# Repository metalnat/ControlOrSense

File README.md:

# ControlOrSense
The project files for my Control Or Sense experiment

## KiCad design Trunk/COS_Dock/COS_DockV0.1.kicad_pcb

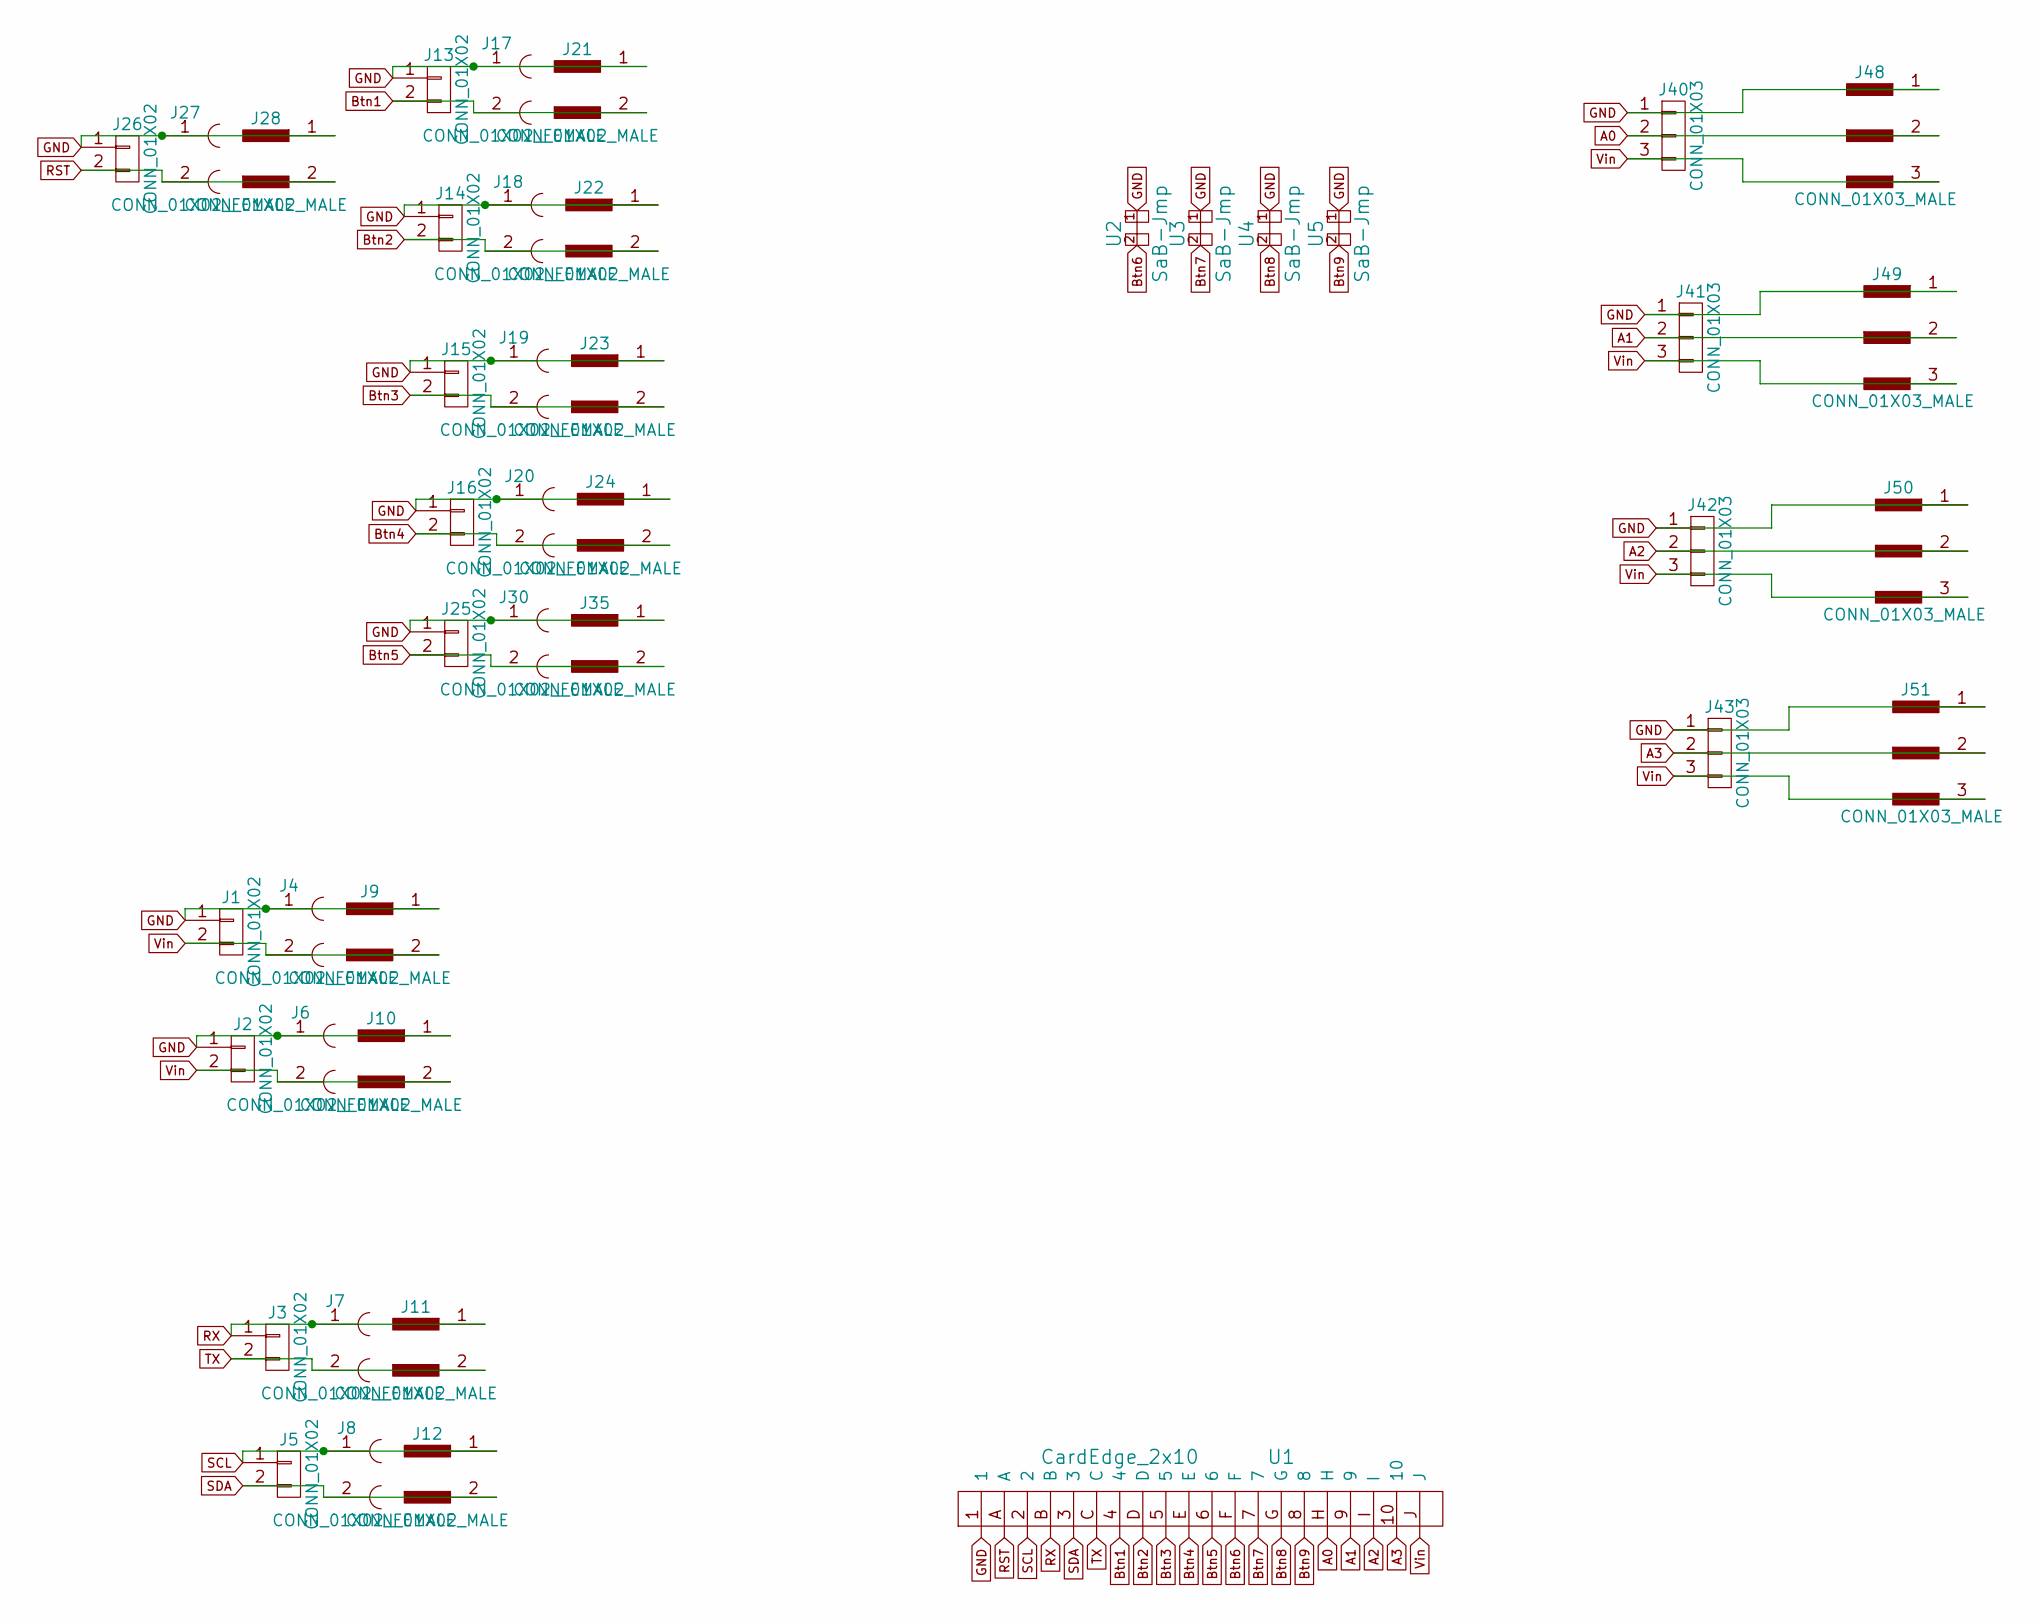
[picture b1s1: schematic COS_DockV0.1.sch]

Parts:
J1, J2, J3, J5, J13, J14, J15, J16, J25, J26: CONN_01X02; Pin_Header_Straight_1x02_Pitch2.54mm
J4, J6, J7, J8, J17, J18, J19, J20, J27, J30: CONN_01X02_FEMALE; SMD-2512_Pol
J9, J10, J11, J12, J21, J22, J23, J24, J28, J35: CONN_01X02_MALE; JST_ZE_BM02B-ZESS-TBT_02x1.5mm_Straight
J40, J41, J42, J43: CONN_01X03; Pin_Header_Straight_1x03_Pitch2.54mm
J48, J49, J50, J51: CONN_01X03_MALE; JST_ZE_BM03B-ZESS-TBT_03x1.5mm_Straight
U1: CardEdge_2x10; CardEdge_10x2_DOCK
U2, U3, U4, U5: SaB-Jmp; GS2

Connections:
A0: J40.2, J48.2, U1.H
A1: J41.2, J49.2, U1.9
A2: J42.2, J50.2, U1.I
A3: J43.2, J51.2, U1.10
Btn1: J13.2, J17.2, J21.2, U1.4
Btn2: J14.2, J18.2, J22.2, U1.D
Btn3: J15.2, J19.2, J23.2, U1.5
Btn4: J16.2, J20.2, J24.2, U1.E
Btn5: J25.2, J30.2, J35.2, U1.6
Btn6: U1.F, U2.2
Btn7: U1.7, U3.2
Btn8: U1.G, U4.2
Btn9: U1.8, U5.2
GND: J1.1, J2.1, J4.1, J6.1, J9.1, J10.1, J13.1, J14.1, J15.1, J16.1, J17.1, J18.1, J19.1, J20.1, J21.1, J22.1, J23.1, J24.1, J25.1, J26.1, J27.1, J28.1, J30.1, J35.1, J40.1, J41.1, J42.1, J43.1, J48.1, J49.1, J50.1, J51.1, U1.1, U2.1, U3.1, U4.1, U5.1
RST: J26.2, J27.2, J28.2, U1.A
RX: J3.1, J7.1, J11.1, U1.B
SCL: J5.1, J8.1, J12.1, U1.2
SDA: J5.2, J8.2, J12.2, U1.3
TX: J3.2, J7.2, J11.2, U1.C
Vin: J1.2, J2.2, J4.2, J6.2, J9.2, J10.2, J40.3, J41.3, J42.3, J43.3, J48.3, J49.3, J50.3, J51.3, U1.J

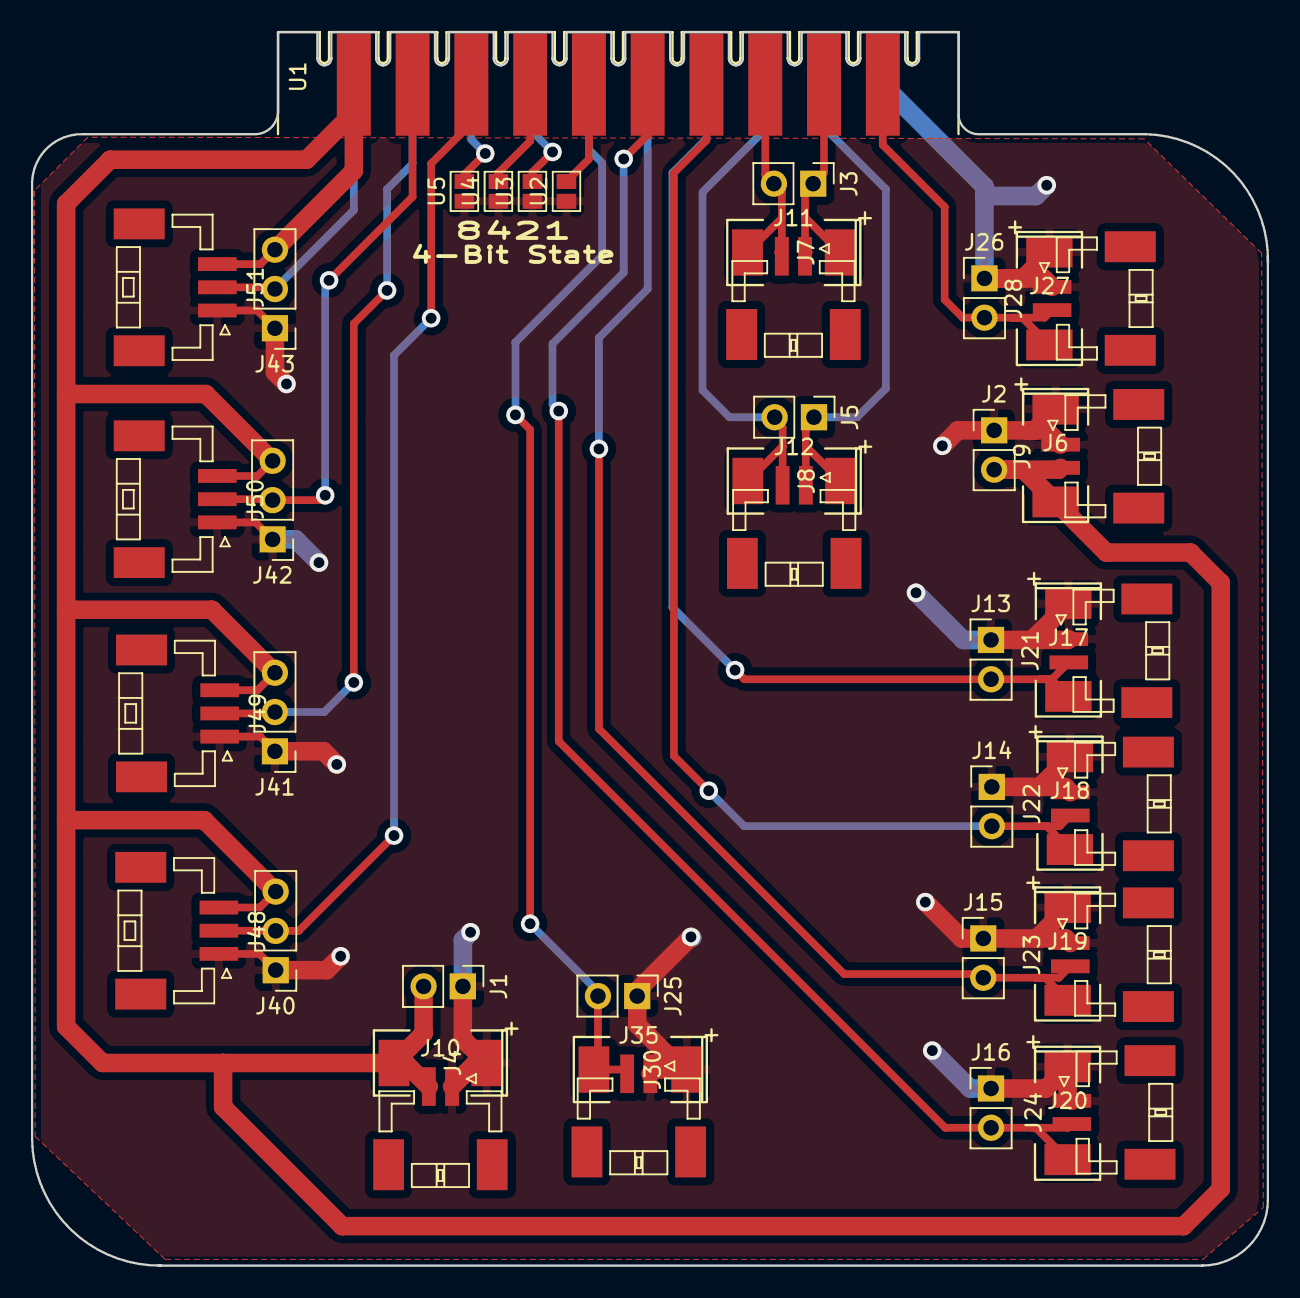
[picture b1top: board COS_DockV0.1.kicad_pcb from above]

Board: 2 copper layers, 79.9 x 79.8 mm, 43 parts (0 on the bottom side), 20 nets.

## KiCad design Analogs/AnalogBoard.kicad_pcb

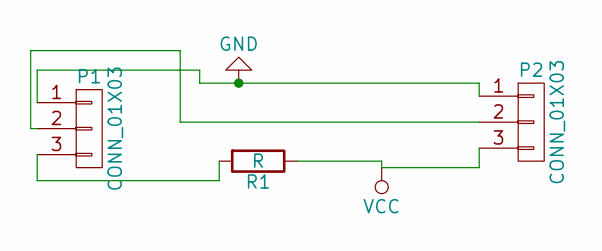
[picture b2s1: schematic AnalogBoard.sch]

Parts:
P1, P2: CONN_01X03; Molex_KK-6410-03_03x2.54mm_Straight
R1: R; R_Axial_DIN0204_L3.6mm_D1.6mm_P7.62mm_Horizontal

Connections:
GND: P1.1, P2.1
unnamed: P1.2, P2.2
unnamed: P1.3, R1.2
VCC: P2.3, R1.1

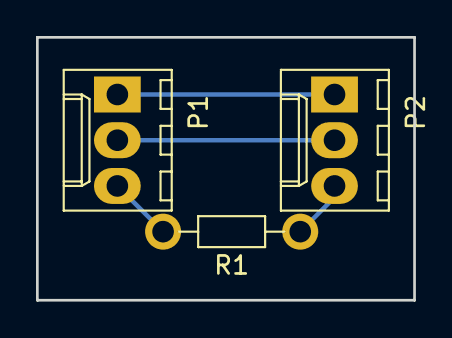
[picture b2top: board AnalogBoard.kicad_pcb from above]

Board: 2 copper layers, 21.0 x 14.6 mm, 3 parts (0 on the bottom side), 4 nets.

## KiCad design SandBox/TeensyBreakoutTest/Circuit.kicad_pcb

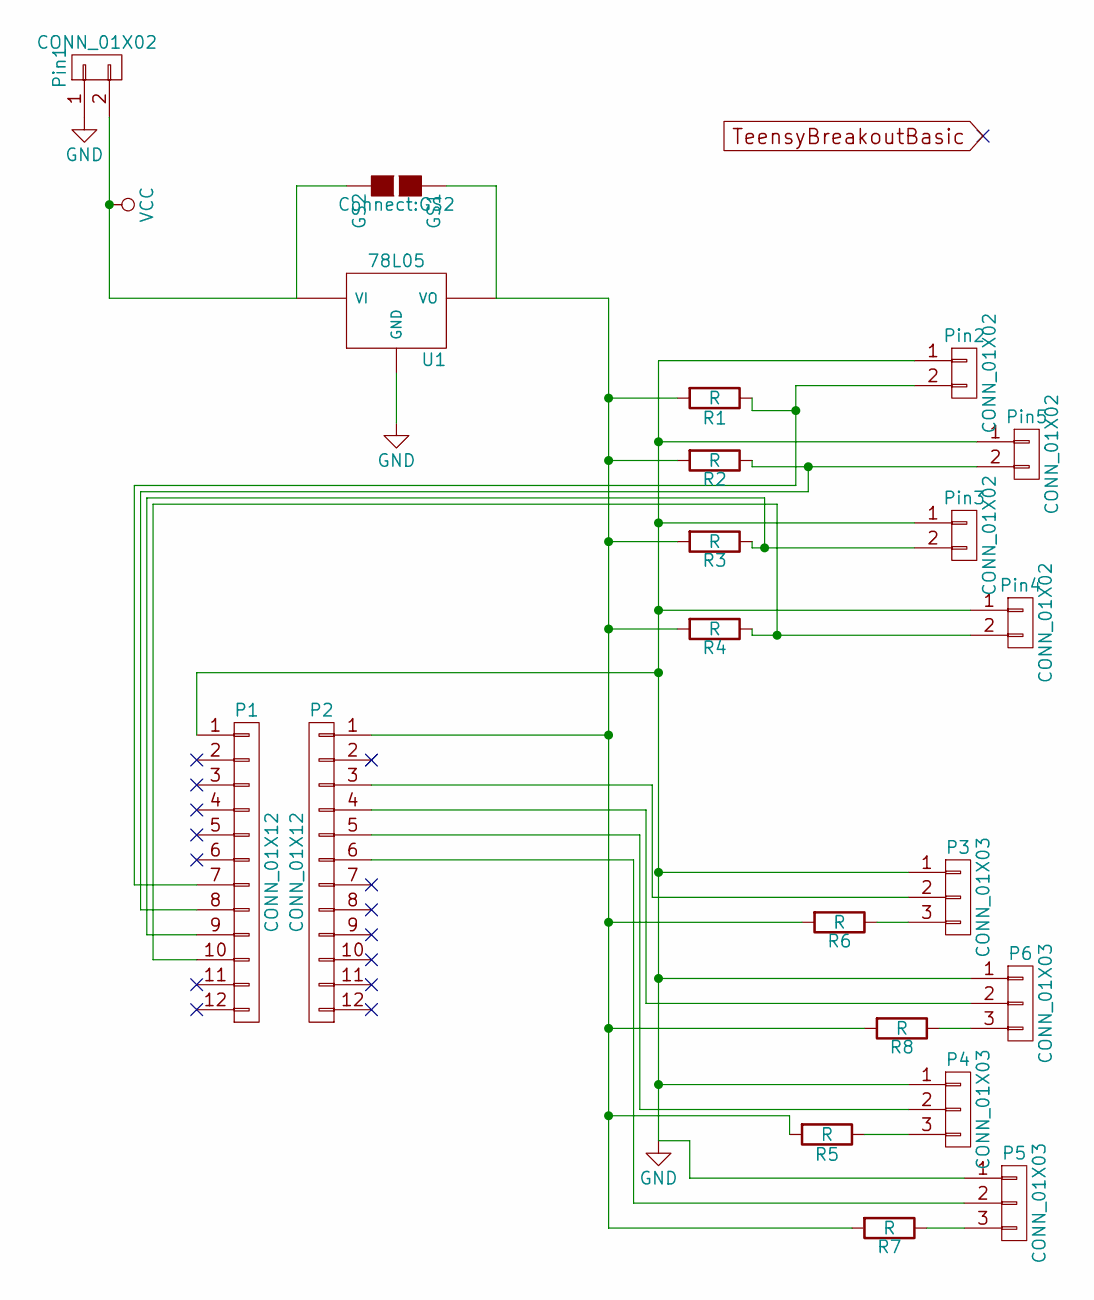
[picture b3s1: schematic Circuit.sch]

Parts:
GS1: GS2
P1, P2: CONN_01X12; Pin_Header_Straight_1x12_Pitch1.27mm
P3, P4, P5, P6: CONN_01X03; Molex_KK-6410-03_03x2.54mm_Straight
Pin1, Pin2, Pin3, Pin4, Pin5: CONN_01X02; Molex_KK-6410-02_02x2.54mm_Straight
R1, R2, R3, R4, R5, R6, R7, R8: R; R_0805_HandSoldering
U1: 78L05; Socket_MOLEX-KK-RM3-96mm_Lock_3pin_straight

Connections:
GND: P1.1, P3.1, P4.1, P5.1, P6.1, Pin1.1, Pin2.1, Pin3.1, Pin4.1, Pin5.1, U1.GND
unnamed: GS1.1 (G1), P2.1, R1.2, R2.2, R3.2, R4.2, R5.2, R6.2, R7.2, R8.2, U1.VO
unnamed: P1.7, Pin2.2, R1.1
unnamed: P1.8, Pin5.2, R2.1
unnamed: P1.9, Pin3.2, R3.1
unnamed: P1.10, Pin4.2, R4.1
unnamed: P2.3, P3.2
unnamed: P2.4, P6.2
unnamed: P2.5, P4.2
unnamed: P2.6, P5.2
unnamed: P3.3, R6.1
unnamed: P4.3, R5.1
unnamed: P5.3, R7.1
unnamed: P6.3, R8.1
VCC: GS1.2 (G2), Pin1.2, U1.VI

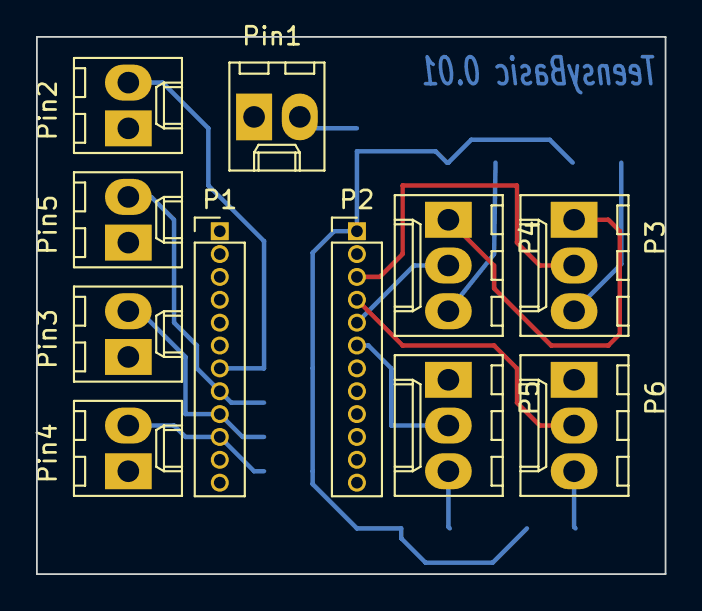
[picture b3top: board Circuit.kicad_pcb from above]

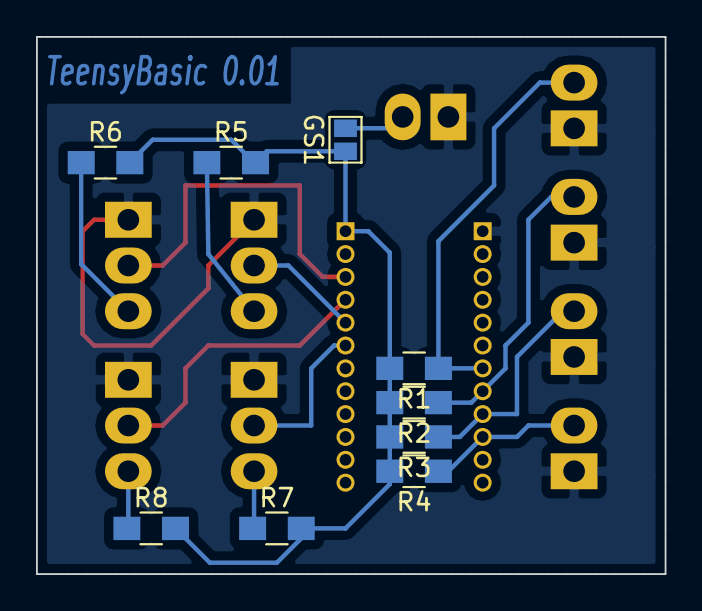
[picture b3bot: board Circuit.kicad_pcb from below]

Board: 2 copper layers, 34.9 x 29.8 mm, 20 parts (9 on the bottom side), 15 nets.

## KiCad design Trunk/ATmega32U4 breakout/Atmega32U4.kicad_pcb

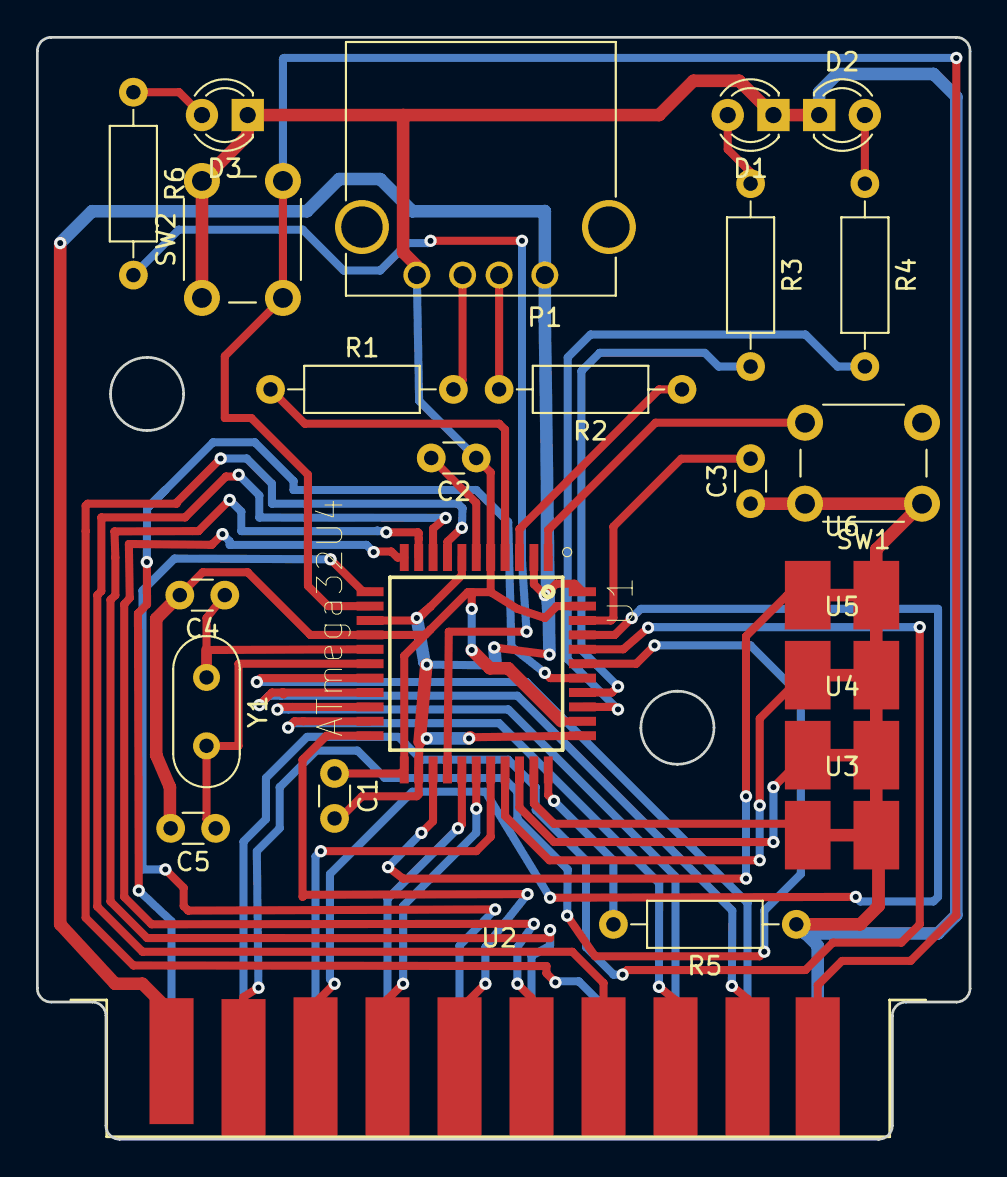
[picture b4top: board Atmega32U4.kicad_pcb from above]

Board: 2 copper layers, 51.8 x 61.2 mm, 24 parts (0 on the bottom side), 36 nets.

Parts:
C1, C2: 1uf; C_Disc_D3.0mm_W1.6mm_P2.50mm
C3: .1uf; C_Disc_D3.0mm_W1.6mm_P2.50mm
C4, C5: 10pf; C_Disc_D3.0mm_W1.6mm_P2.50mm
D1: LedIndicator01; LED_D3.0mm
D2: LedIndicator02; LED_D3.0mm
D3: Led_Small; LED_D3.0mm
P1: USB; USB_A
R1, R2: 22R; R_Axial_DIN0207_L6.3mm_D2.5mm_P10.16mm_Horizontal
R3, R4: 220; R_Axial_DIN0207_L6.3mm_D2.5mm_P10.16mm_Horizontal
R5, R6: 1K; R_Axial_DIN0207_L6.3mm_D2.5mm_P10.16mm_Horizontal
SW1: BtnLocal; SW_PUSH_6mm
SW2: Reset Btn; SW_PUSH_6mm
U1: ATmega32U4; QFP80P1200X1200X120-44N
U2: CardEdge_2x10; CardEdge_10x2
U3, U4, U5, U6: SlashAndBurn-Jumper
Y1: 16MHz; Crystal_HC52-6mm_Vertical

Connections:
+3V3: C2.2, U1.6
+5V: C1.2, P1.1, U1.2, U1.7, U1.14, U1.24, U1.34, U1.44, U2.J
A0: U1.41, U2.H
A1: U1.40, U2.9
A2: U1.39, U2.I
A3: U1.38, U2.10
Btn1: U1.8, U2.4
Btn2: U1.9, U2.D
Btn3: U1.10, U2.5
Btn4: U1.11, U2.E
Btn5: U1.12, U2.6
Btn6: U1.22, U2.F
Btn7: U1.27, U2.7
Btn8: U1.28, U2.G
Btn9: U1.29, U2.8
GND: C1.1, C2.1, C3.1, C4.2, C5.2, D1.1, D2.1, D3.1, P1.4, R5.1, SW1.1, SW2.1, U1.5, U1.15, U1.23, U1.25, U1.30, U1.31, U1.32, U1.35, U1.43, U2.1, U3.1, U3.2, U4.1, U4.2, U5.1, U5.2, U6.1, U6.2
unnamed: C3.2, U1.42
unnamed: C4.1, U1.16, Y1.1
unnamed: C5.1, U1.17, Y1.2
unnamed: D1.2, R3.1
unnamed: D2.2, R4.1
unnamed: D3.2, R6.1
unnamed: P1.2, R2.2
unnamed: P1.3, R1.2
unnamed: R1.1, U1.4
unnamed: R2.1, U1.3
unnamed: R3.2, U1.37
unnamed: R4.2, U1.36
unnamed: R5.2, U1.33
unnamed: R6.2, U1.26
unnamed: SW1.2, U1.1
RX: U1.20, U2.3
Reset: SW2.2, U1.13, U2.A
SCL: U1.18, U2.2
SDA: U1.19, U2.B
TX: U1.21, U2.C

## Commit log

2017-10-27 Attempt number two to upload assets
    this will include an analog and digital board, one dock board, and one main with through hole components, plus any sandbox teensy board I may have made.
    -Also included base arduino code. based on the teensy joystick example with remapping started for pin layout for matching up to this board.
    ~Metal
